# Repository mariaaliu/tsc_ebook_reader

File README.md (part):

## Aliu Maria-Denisa
#### 335CC
<br><br>

## Descriere generală
Acest proiect reprezintă un eBook Reader minimalist, denumit **OpenBook**, construit pe baza platformei **ESP32-C6** și echipat cu un ecran e-paper de **7.5 inch**, o baterie Li-Po, încărcare prin USB-C și butoane fizice pentru control.

Dispozitivul este proiectat să fie eficient energetic și ușor de utilizat, având o interfață simplă controlată prin GPIO-uri, cu funcții de afișare a textelor pentru o experiență de e-reading optimă.

---

<br><br>

## Cuprins
- [Specificații](#specificații)
- [Pași de implementare](#pași-de-implementare)
- [Diagramă Bloc](#diagramă-bloc)
- [BOM (Bill Of Materials)](#bom-bill-of-materials)
- [Descrierea hardware – Conexiuni și Funcționalitate](#descrierea-hardware--conexiuni-și-funcționalitate)
- [Pinout ESP32-C6](#pinout-esp32-c6)
- [Estimare Consum](#estimare-consum)
- [Vederi ale Prototipului](#vederi-ale-prototipului)

---

#### Specificații

- **MCU**: ESP32-C6 (Wi-Fi 6, BLE, RISC-V)
- **Ecran**: 7.8" E-paper
- **Stocare**: Slot microSD
- **Conectivitate**: Qwiic, USB-C
- **Senzori**: BME680 (temperatură, umiditate, gaz, presiune)
- **Alimentare**: Baterie Li-Po 3.7V, încărcare prin USB-C
- **RTC**: extern pentru consum redus în deep sleep
- **Control**: 3 butoane + LED

---
#### Pași de implementare:

- realizarea schemei electrice
- poziționarea pieselor pe PCB 2D
- realizarea modelului 3D
- simularea încadrării pieselor în carcasa finală
- prezentarea produsului final simulat
  
---

## Diagramă Bloc

```mermaid
graph TD;
    
    USB["USB-C Connector & ESD Protection"] -->|VBUS| CHG
    BATT["Li-Po Battery"] -->|VBAT| CHG["Battery Charging Controller (MCP73831)"]
    USB -->|VBUS pass-through| LDO["LDO Voltage Regulator (XC6220)"]
    USB -->|USB| ESP["ESP32-C6 MICROCONTROLLER Wi-Fi (MCU Central)"]
    CHG -->|VBAT| LDO
    LDO -->|3.3V| ESP["ESP32-C6 MICROCONTROLLER Wi-Fi (MCU Central)"]

    ESP -->|I2C| RTC["RTC Module (DS3231SN)"]
    ESP -->|I2C| BME["Environmental Sensor (BME680)"]

    ESP -->|SPI| FLASH["External NOR Flash (W25Q512)"]
    ESP -->|SPI| EPD_HEADER["E-Paper Display Header"]
    ESP -->|SPI| SD["MicroSD Card"]
    ESP -->|GPIO| BUTTONS["BOOT, CHANGE, RESET Buttons"]
    ESP -->|GPIO| VSUP["Voltage Supervisor + Reset/Boot IO"]

    EPD_HEADER -->|Power, SPI| EPD_DRIVER["E-Paper Drive Circuit"]
    EPD_DRIVER -->|Type Config| DISP_SEL["Display Type Selector"]
    EPD_DRIVER -->|High Voltage| EPD_POW["EPD Power Circuit"]

    I2C_CONN["Qwiic / Stemma QT"] -->|I2C| ESP
    BAT_LVL["Battery Charge Level"] -->|I2C| ESP
    SERCOM["RX/TX Serial Communication"] --> ESP
```

## BOM (Bill Of Materials)

| Componentă      | Proptietăți                 | Package                                | Link Purchase              | Datasheet                | 
|----------------|-------------------------|----------------------------------------|-----------------------------------|-----------------------------|
| BOOT_BUTTON    | BUTTON_CUSYOMV1         | MYBUTTON | https://industry.panasonic.com/global/en/products/control/switch/light-touch/number/evqpuj02k | https://www.es.co.th/Schemetic/PDF/EVQPUX02K.PDF|
| C1            | 100nF                  | ESP32_WROVER_EAGLE-LTSPICE_C0402       | https://componentsearchengine.com/part-view/CC0402MRX5R5BB106/YAGEO | https://www.farnell.com/datasheets/2167237.pdf|
| C10            | 100nF                  | ESP32_WROVER_EAGLE-LTSPICE_C0402       | https://componentsearchengine.com/part-view/CC0402MRX5R5BB106/YAGEO | https://www.farnell.com/datasheets/2167237.pdf|
| C10_SUPERCAP   | CPH3225A               | CAPCP3225X100N  | https://www.snapeda.com/parts/CPH3225A/Seiko+Instruments/view-part/?ref=eda | https://www.eaton.com/content/dam/eaton/products/electronic-components/resources/data-sheet/eaton-xt-supercapacitors-cylindrical-cells-data-sheet.pdf|
| C1_BAT         | 4.7uF                  | ESP32_WROVER_EAGLE-LTSPICE_C0402       | https://componentsearchengine.com/part-view/CC0402MRX5R5BB106/YAGEO | https://www.datasheets.com/part-details/ctc4-c-4-7uf-20--25v-exxelia-group-407015684#datasheet?srsltid=AfmBOopSxVESrdZ-JeJFYRuFdBfwBIXZfFTXDnvi5T4sC5myfTVXPCBc|
| C1_BAT1        | 4.7uF                  | ESP32_WROVER_EAGLE-LTSPICE_C0402       | https://componentsearchengine.com/part-view/CC0402MRX5R5BB106/YAGEO | https://www.datasheets.com/part-details/ctc4-c-4-7uf-20--25v-exxelia-group-407015684#datasheet?srsltid=AfmBOopSxVESrdZ-JeJFYRuFdBfwBIXZfFTXDnvi5T4sC5myfTVXPCBc|
| C1_BAT2        | 4.7uF                  | ESP32_WROVER_EAGLE-LTSPICE_C0402       | https://componentsearchengine.com/part-view/CC0402MRX5R5BB106/YAGEO | https://www.datasheets.com/part-details/ctc4-c-4-7uf-20--25v-exxelia-group-407015684#datasheet?srsltid=AfmBOopSxVESrdZ-JeJFYRuFdBfwBIXZfFTXDnvi5T4sC5myfTVXPCBc|
| C2             | 100nF                  | ESP32_WROVER_EAGLE-LTSPICE_C0402       | https://componentsearchengine.com/part-view/CC0402MRX5R5BB106/YAGEO | https://www.farnell.com/datasheets/2167237.pdf|
| C2_BAT        | 4.7uF                  | ESP32_WROVER_EAGLE-LTSPICE_C0402       | https://componentsearchengine.com/part-view/CC0402MRX5R5BB106/YAGEO | https://www.datasheets.com/part-details/ctc4-c-4-7uf-20--25v-exxelia-group-407015684#datasheet?srsltid=AfmBOopSxVESrdZ-JeJFYRuFdBfwBIXZfFTXDnvi5T4sC5myfTVXPCBc|
| C3            | 100uF                  | RCL_CT3528 | https://eu.mouser.com/ProductDetail/KYOCERA-AVX/F910J107MBAAJ6?qs=PqoDHHvF649LraCA%2FjeGXg%3D%3D | https://www.farnell.com/datasheets/2167237.pdf|
| C4             | 4.7uF/25V              | ESP32_WROVER_EAGLE-LTSPICE_C0402       | https://componentsearchengine.com/part-view/CC0402MRX5R5BB106/YAGEO | https://www.datasheets.com/part-details/ctc4-c-4-7uf-20--25v-exxelia-group-407015684#datasheet?srsltid=AfmBOopSxVESrdZ-JeJFYRuFdBfwBIXZfFTXDnvi5T4sC5myfTVXPCBc|
| C4_USB         | 100nF                  | ESP32_WROVER_EAGLE-LTSPICE_C0402       | https://componentsearchengine.com/part-view/CC0402MRX5R5BB106/YAGEO | https://www.farnell.com/datasheets/2167237.pdf|
| C5             | 1uF                    | ESP32_WROVER_EAGLE-LTSPICE_C0402       | https://componentsearchengine.com/part-view/CC0402MRX5R5BB106/YAGEO | https://www.farnell.com/datasheets/2167237.pdf|
| C5_USB         | 4.7uF                  | ESP32_WROVER_EAGLE-LTSPICE_C0402       | https://componentsearchengine.com/part-view/CC0402MRX5R5BB106/YAGEO | https://www.datasheets.com/part-details/ctc4-c-4-7uf-20--25v-exxelia-group-407015684#datasheet?srsltid=AfmBOopSxVESrdZ-JeJFYRuFdBfwBIXZfFTXDnvi5T4sC5myfTVXPCBc|
| C6             | 100nF                  | ESP32_WROVER_EAGLE-LTSPICE_C0402       | https://componentsearchengine.com/part-view/CC0402MRX5R5BB106/YAGEO | https://www.farnell.com/datasheets/2167237.pdf|
| C7             | 10uF                   | ESP32_WROVER_EAGLE-LTSPICE_C0402       | https://componentsearchengine.com/part-view/CC0402MRX5R5BB106/YAGEO | https://www.farnell.com/datasheets/2167237.pdf|
| C8             | 100nF                  | ESP32_WROVER_EAGLE-LTSPICE_C0402       | https://componentsearchengine.com/part-view/CC0402MRX5R5BB106/YAGEO | https://www.farnell.com/datasheets/2167237.pdf|
| C9            | 100nF                  | ESP32_WROVER_EAGLE-LTSPICE_C0402       | https://componentsearchengine.com/part-view/CC0402MRX5R5BB106/YAGEO | https://www.farnell.com/datasheets/2167237.pdf|
| CHANGE_BUTTON  | BUTTON_CUSYOMV1         | MYBUTTON | https://industry.panasonic.com/global/en/products/control/switch/light-touch/number/evqpuj02k | https://www.es.co.th/Schemetic/PDF/EVQPUX02K.PDF|
| CHG_LED        |                        | ADAFRUIT_CHIP-LED0603                  | https://www.snapeda.com/parts/KP-1608SURCK/Kingbright/view-part/?ref=search&t=LED%200603 | https://www.farnell.com/datasheets/1760130.pdf|
| C_DELAY        | 100nF                  | ESP32_WROVER_EAGLE-LTSPICE_C0402       | https://componentsearchengine.com/part-view/CC0402MRX5R5BB106/YAGEO | https://www.farnell.com/datasheets/2167237.pdf|
| D1             | USBLC6-2SC6Y            | SOT95P280X145-6N                       | https://www.snapeda.com/parts/USBLC6-2SC6Y/STMicroelectronics/view-part/?ref=eda | https://www.alldatasheet.com/view.jsp?Searchword=Usblc6-2sc6%20datasheet&gad_source=1&gclid=Cj0KCQjwqcO_BhDaARIsACz62vNXZrpQv2LPEwLifCXR-Z6ow5Jz23VCwAl6sagpvX4qBsG8mq23hT8aAgWJEALw_wcB|
| D10            | PGB1010603MR            | DIOC1608X36N                           | https://www.snapeda.com/parts/PGB1010603MR/Littelfuse/view-part/?ref=eda | https://www.alldatasheet.com/view.jsp?Searchword=Pgb1010603mr&gad_source=1&gclid=Cj0KCQjwqcO_BhDaARIsACz62vM1VI-TQZSchByLeU1DA3nQWoILlr1ci-3FtcNGSAGQc69Pgj3MI4oaAjWKEALw_wcB|
| D11            | PGB1010603MR            | DIOC1608X36N                           | https://www.snapeda.com/parts/PGB1010603MR/Littelfuse/view-part/?ref=eda | https://www.alldatasheet.com/view.jsp?Searchword=Pgb1010603mr&gad_source=1&gclid=Cj0KCQjwqcO_BhDaARIsACz62vM1VI-TQZSchByLeU1DA3nQWoILlr1ci-3FtcNGSAGQc69Pgj3MI4oaAjWKEALw_wcB|
| D12            | PGB1010603MR            | DIOC1608X36N                           | https://www.snapeda.com/parts/PGB1010603MR/Littelfuse/view-part/?ref=eda | https://www.alldatasheet.com/view.jsp?Searchword=Pgb1010603mr&gad_source=1&gclid=Cj0KCQjwqcO_BhDaARIsACz62vM1VI-TQZSchByLeU1DA3nQWoILlr1ci-3FtcNGSAGQc69Pgj3MI4oaAjWKEALw_wcB|
| D2             | ESP32_WROVER_AVX---SD0805S020S1R0_AVX_SD0805S020S1R0_0 | ESP32_WROVER_AVX---SD0805S020S1R0_AVX_SD0805S020S1R0_0 | https://ro.mouser.com/ProductDetail/KYOCERA-AVX/SD0805S020S1R0?qs=jCA%252BPfw4LHbpkAoSnwrdjw%3D%3D&utm_id=6470900573&utm_source=google&utm_medium=cpc&utm_marketing_tactic=emeacorp&gad_source=1&gclid=Cj0KCQjwqcO_BhDaARIsACz62vPEfi9ntBpuuK1LHM6sMAyEc2S6XwGXFRcoYK5gKMYya27spaEhkKEaAkeQEALw_wcB | https://www.alldatasheet.com/datasheet-pdf/pdf/925781/AVX/SD0805S020S1R0.html|
| D3             | MBR0530                 | SOD3716X135N                           | https://www.snapeda.com/parts/MBR0530/Onsemi/view-part/?ref=eda | https://www.alldatasheet.com/view.jsp?Searchword=Mbr0530%20datasheet&gad_source=1&gclid=Cj0KCQjwqcO_BhDaARIsACz62vP1swtUgHHaBr1h1Ae3TYdeqhmQC4x2pEdoGRj9oflsija9HAEBlBMaAvdlEALw_wcB|
| D4             | MBR0530                 | SOD3716X135N                           | https://www.snapeda.com/parts/MBR0530/Onsemi/view-part/?ref=eda | https://www.alldatasheet.com/view.jsp?Searchword=Mbr0530%20datasheet&gad_source=1&gclid=Cj0KCQjwqcO_BhDaARIsACz62vP1swtUgHHaBr1h1Ae3TYdeqhmQC4x2pEdoGRj9oflsija9HAEBlBMaAvdlEALw_wcB|
| D5             | MBR0530                 | SOD3716X135N                           | https://www.snapeda.com/parts/MBR0530/Onsemi/view-part/?ref=eda | https://www.alldatasheet.com/view.jsp?Searchword=Mbr0530%20datasheet&gad_source=1&gclid=Cj0KCQjwqcO_BhDaARIsACz62vP1swtUgHHaBr1h1Ae3TYdeqhmQC4x2pEdoGRj9oflsija9HAEBlBMaAvdlEALw_wcB|
| D6             | PGB1010603MR            | DIOC1608X36N                           | https://www.snapeda.com/parts/PGB1010603MR/Littelfuse/view-part/?ref=eda | https://www.alldatasheet.com/view.jsp?Searchword=Pgb1010603mr&gad_source=1&gclid=Cj0KCQjwqcO_BhDaARIsACz62vM1VI-TQZSchByLeU1DA3nQWoILlr1ci-3FtcNGSAGQc69Pgj3MI4oaAjWKEALw_wcB|
| D7             | ESP32_WROVER_AVX---SD0805S020S1R0_AVX_SD0805S020S1R0_0 | ESP32_WROVER_AVX---SD0805S020S1R0_AVX_SD0805S020S1R0_0 | https://eu.mouser.com/ProductDetail/KYOCERA-AVX/SD0805S020S1R0?qs=jCA%252BPfw4LHbpkAoSnwrdjw%3D%3D | https://www.alldatasheet.com/datasheet-pdf/pdf/925781/AVX/SD0805S020S1R0.html|
| D8             | PGB1010603MR            | DIOC1608X36N                           | https://www.snapeda.com/parts/PGB1010603MR/Littelfuse/view-part/?ref=eda | https://www.alldatasheet.com/view.jsp?Searchword=Pgb1010603mr&gad_source=1&gclid=Cj0KCQjwqcO_BhDaARIsACz62vM1VI-TQZSchByLeU1DA3nQWoILlr1ci-3FtcNGSAGQc69Pgj3MI4oaAjWKEALw_wcB|
| D9             | PGB1010603MR            | DIOC1608X36N                           | https://www.snapeda.com/parts/PGB1010603MR/Littelfuse/view-part/?ref=eda |   https://www.alldatasheet.com/view.jsp?Searchword=Pgb1010603mr&gad_source=1&gclid=Cj0KCQjwqcO_BhDaARIsACz62vM1VI-TQZSchByLeU1DA3nQWoILlr1ci-3FtcNGSAGQc69Pgj3MI4oaAjWKEALw_wcB|
| EPD_C1         | 1uF/50V                | ESP32_WROVER_EAGLE-LTSPICE_C0402       | https://componentsearchengine.com/part-view/CC0402MRX5R5BB106/YAGEO | https://www.alldatasheet.com/view.jsp?Searchword=Cc0402&gad_source=1&gclid=Cj0KCQjwqcO_BhDaARIsACz62vOHh9yg0g_xZhcu9_CEKANvUYtGv2kGtbzHYiw6TGDxPK-tL5UACRUaArTeEALw_wcB|
| EPD_C10        | 1uF/50V                | ESP32_WROVER_EAGLE-LTSPICE_C0402       | https://componentsearchengine.com/part-view/CC0402MRX5R5BB106/YAGEO | https://www.alldatasheet.com/view.jsp?Searchword=Cc0402&gad_source=1&gclid=Cj0KCQjwqcO_BhDaARIsACz62vOHh9yg0g_xZhcu9_CEKANvUYtGv2kGtbzHYiw6TGDxPK-tL5UACRUaArTeEALw_wcB|
| EPD_C11        | 1uF/50V                | ESP32_WROVER_EAGLE-LTSPICE_C0402       | https://componentsearchengine.com/part-view/CC0402MRX5R5BB106/YAGEO | https://www.farnell.com/datasheets/2167237.pdf|
| EPD_C12        | 1uF/50V                | ESP32_WROVER_EAGLE-LTSPICE_C0402       |   https://componentsearchengine.com/part-view/CC0402MRX5R5BB106/YAGEO | https://www.farnell.com/datasheets/2167237.pdf|
| EPD_C2         | 1uF/50V                | ESP32_WROVER_EAGLE-LTSPICE_C0402       |   https://componentsearchengine.com/part-view/CC0402MRX5R5BB106/YAGEO | https://www.farnell.com/datasheets/2167237.pdf|
| EPD_C5         | 1uF/50V                | ESP32_WROVER_EAGLE-LTSPICE_C0402       |   https://componentsearchengine.com/part-view/CC0402MRX5R5BB106/YAGEO | https://www.farnell.com/datasheets/2167237.pdf|
| EPD_C6         | 1uF/50V                | ESP32_WROVER_EAGLE-LTSPICE_C0402       |   https://componentsearchengine.com/part-view/CC0402MRX5R5BB106/YAGEO | https://www.farnell.com/datasheets/2167237.pdf|
| EPD_C7         | 1uF/50V                | ESP32_WROVER_EAGLE-LTSPICE_C0402       |   https://componentsearchengine.com/part-view/CC0402MRX5R5BB106/YAGEO | https://www.farnell.com/datasheets/2167237.pdf|
| EPD_C8         | 1uF/50V                | ESP32_WROVER_EAGLE-LTSPICE_C0402       |   https://componentsearchengine.com/part-view/CC0402MRX5R5BB106/YAGEO | https://www.farnell.com/datasheets/2167237.pdf|
| EPD_C9         | 1uF/50V                | ESP32_WROVER_EAGLE-LTSPICE_C0402       |   https://componentsearchengine.com/part-view/CC0402MRX5R5BB106/YAGEO | https://www.farnell.com/datasheets/2167237.pdf|
| IC1            | BD5229G-TR             | SOT95P280X125-5N                       | https://componentsearchengine.com/part-view/BD5229G-TR/ROHM%20Semiconductor | https://www.alldatasheet.com/datasheet-pdf/pdf/562784/ROHM/BD5229G-TR.html|
| IC4            | XC6220A331MR-G         | SOT95P280X120-5N | https://componentsearchengine.com/part-view/XC6220A331MR-G/Torex | https://www.alldatasheet.com/view.jsp?Searchword=Xc6220&gad_source=1&gclid=Cj0KCQjwqcO_BhDaARIsACz62vNFXNXymZGlzcmkfMZCs0YXLAkJ5yWCPMtu7VvrTb50o02U6EU8bI8aAu8CEALw_wcB|
| J1        | FH34SRJ-24S-0.5SH_99_ | FH34SRJ24S05SH99                               | https://componentsearchengine.com/part-view/FH34SRJ-24S-0.5SH(99)/Hirose | https://ro.mouser.com/ProductDetail/Hirose-Connector/FH34S-24S-05SH99?qs=sGAEpiMZZMtarqWRZQNdzRgjNobWj1V%252b&srsltid=AfmBOopOc7xnQo8WmFAadUKxs2Pv_ZRqS0lJLFK245RRjT5g5CQNT84v|
| J2        | SAMACSYS_PARTS_USB4110-GF-A | SAMACSYS_PARTS_USB4110GFA                     | https://componentsearchengine.com/part-view/USB4110-GF-A/GCT%20(GLOBAL%20CONNECTOR%20TECHNOLOGY) | https://www.lcsc.com/datasheet/lcsc_datasheet_2410121848_Global-Connector-Technology-USB4110-GF-A_C5143397.pdf|
| J3        | QWIIC_RIGHT_ANGLE | JST04_1MM_RA                                  | https://eu.mouser.com/ProductDetail/Adafruit/4208?qs=PzGy0jfpSMtbScLbr0L5dw%3D%3D | ...|
| J4        | 112A-TAAR-R03_ATTEND | 112ATAARR03ATTEND                             | https://store.comet.srl.ro/Catalogue/Product/43497/ | https://www.lcsc.com/datasheet/lcsc_datasheet_2411220717_Attend-Technology-112A-TAAR-R03_C6970445.pdf|
| L1        | 68uH            | IND_4828-WE-TPC_WRE                           | https://eu.mouser.com/ProductDetail/Wurth-Elektronik/744043680?qs=PGXP4M47uW6VkZq%252BkzjrHA%3D%3D | https://in.element14.com/c/passive-components/inductors/power-inductors/smd-power-inductors?inductance=68uh&srsltid=AfmBOoqYXGbL9sGdZ46Hro8CihzXM-LXkKuWlFwNsDA_NlrY7XGM2FaG|
| MCP73831  | ESP32_WROVER_SPARKFUN-IC-POWER_MCP73831 | ESP32_WROVER_SPARKFUN-IC-POWER_SOT23-5 | https://eu.mouser.com/ProductDetail/Microchip-Technology/MCP73831T-2ACI-OT?qs=yUQqVecv4qvbBQBGbHx0Mw%3D%3D | https://www.alldatasheet.com/view.jsp?Searchword=Mcp73831%20datasheet&gad_source=1&gclid=Cj0KCQjwqcO_BhDaARIsACz62vNE_GnTDdT47-u9Q2OgRK9TX-D7V258Eoba7KxX2pQKwTPrbfjDHwUaAgovEALw_wcB|
| PFMF.050.1| ESP32C6_VARISTORCN1812 | ESP32C6_VARISTOR_CT/CN1812                    | https://www.mouser.co.uk/ProductDetail/EPCOS-TDK/B72520T0350K062?qs=dEfas%2FXlABIszF52uu7vrg%3D%3D | https://www.alldatasheet.com/datasheet-pdf/pdf/356683/SCHURTER/PFMF.050.2.html|
| Q1        | 20V/4.2A/52mΩ/1.4W | ESP32_WROVER_SPARKFUN-DISCRETESEMI_SOT23-3    | https://componentsearchengine.com/part-view/DMG2305UX-7/Diodes%20Incorporated | https://www.alldatasheet.com/view.jsp?Searchword=Dmg2305ux%20datasheet&gad_source=1&gclid=Cj0KCQjwqcO_BhDaARIsACz62vMQW1FwcgD0y0qdHMHKzUlJHlz1eBpHMgg3QfZKxp4WrlQYG_-XCGgaApFcEALw_wcB|
| Q2        | 20V/4.2A/52mΩ/1.4W | ESP32_WROVER_SPARKFUN-DISCRETESEMI_SOT23-3    | https://componentsearchengine.com/part-view/DMG2305UX-7/Diodes%20Incorporated | https://www.alldatasheet.com/view.jsp?Searchword=Dmg2305ux%20datasheet&gad_source=1&gclid=Cj0KCQjwqcO_BhDaARIsACz62vMQW1FwcgD0y0qdHMHKzUlJHlz1eBpHMgg3QfZKxp4WrlQYG_-XCGgaApFcEALw_wcB|
| Q3        | SI1308EDL-T1-GE3 | SOT65P210X110-3N                              | https://www.snapeda.com/parts/SI1308EDL-T1-GE3/Vishay+Siliconix/view-part/?ref=eda | https://www.alldatasheet.com/view.jsp?Searchword=Si1308edl&gad_source=1&gclid=Cj0KCQjwqcO_BhDaARIsACz62vM_bGjumR2fFnx6qeTFOw_xlZ569sW-bMnlphTnUfPy48QznN7oXRgaAuROEALw_wcB|
| R1        | 10K             | ESP32_WROVER_EAGLE-LTSPICE_R0402              | https://componentsearchengine.com/part-view/R0402%201%25%20100%20K%20(RC0402FR-07100KL)/YAGEO | https://ro.farnell.com/c/passive-components/resistors-fixed-value/chip-smd-resistors?resistance=10kohm&srsltid=AfmBOoppk2KzsJ9X9eQ3Cprqx-aidJD_GTPJgWaEEgH3df9fBymJm3mo|
| R10       | 10K             | ESP32_WROVER_EAGLE-LTSPICE_R0402              | https://componentsearchengine.com/part-view/R0402%201%25%20100%20K%20(RC0402FR-07100KL)/YAGEO | https://ro.farnell.com/c/passive-components/resistors-fixed-value/chip-smd-resistors?resistance=10kohm&srsltid=AfmBOoppk2KzsJ9X9eQ3Cprqx-aidJD_GTPJgWaEEgH3df9fBymJm3mo|
| R1_BAT    | 200             | ESP32_WROVER_EAGLE-LTSPICE_R0402              | https://ro.mouser.com/c/passive-components/resistors/smd-resistors-chip-resistors/?case%20code%20-%20in=0402&resistance=200%20Ohms&srsltid=AfmBOoo-6O-URQcmQGAwWvWkSloJBGjVxIwzoZir5TS3KZAaaRmw5_VT | https://www.farnell.com/datasheets/2167237.pdf|
| R1_PINH   | 10K             | ESP32_WROVER_EAGLE-LTSPICE_R0402              | https://componentsearchengine.com/part-view/R0402%201%25%20100%20K%20(RC0402FR-07100KL)/YAGEO | https://ro.farnell.com/c/passive-components/resistors-fixed-value/chip-smd-resistors?resistance=10kohm&srsltid=AfmBOoppk2KzsJ9X9eQ3Cprqx-aidJD_GTPJgWaEEgH3df9fBymJm3mo|
| R1_PINH1  | 10K             | ESP32_WROVER_EAGLE-LTSPICE_R0402              | https://componentsearchengine.com/part-view/R0402%201%25%20100%20K%20(RC0402FR-07100KL)/YAGEO | https://ro.farnell.com/c/passive-components/resistors-fixed-value/chip-smd-resistors?resistance=10kohm&srsltid=AfmBOoppk2KzsJ9X9eQ3Cprqx-aidJD_GTPJgWaEEgH3df9fBymJm3mo|
| R1_PWRUSB | 100k            | ESP32_WROVER_EAGLE-LTSPICE_R0402              | https://componentsearchengine.com/part-view/R0402%201%25%20100%20K%20(RC0402FR-07100KL)/YAGEO | https://ro.farnell.com/c/passive-components/resistors-fixed-value/chip-smd-resistors?resistance=10kohm&srsltid=AfmBOoppk2KzsJ9X9eQ3Cprqx-aidJD_GTPJgWaEEgH3df9fBymJm3mo|
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
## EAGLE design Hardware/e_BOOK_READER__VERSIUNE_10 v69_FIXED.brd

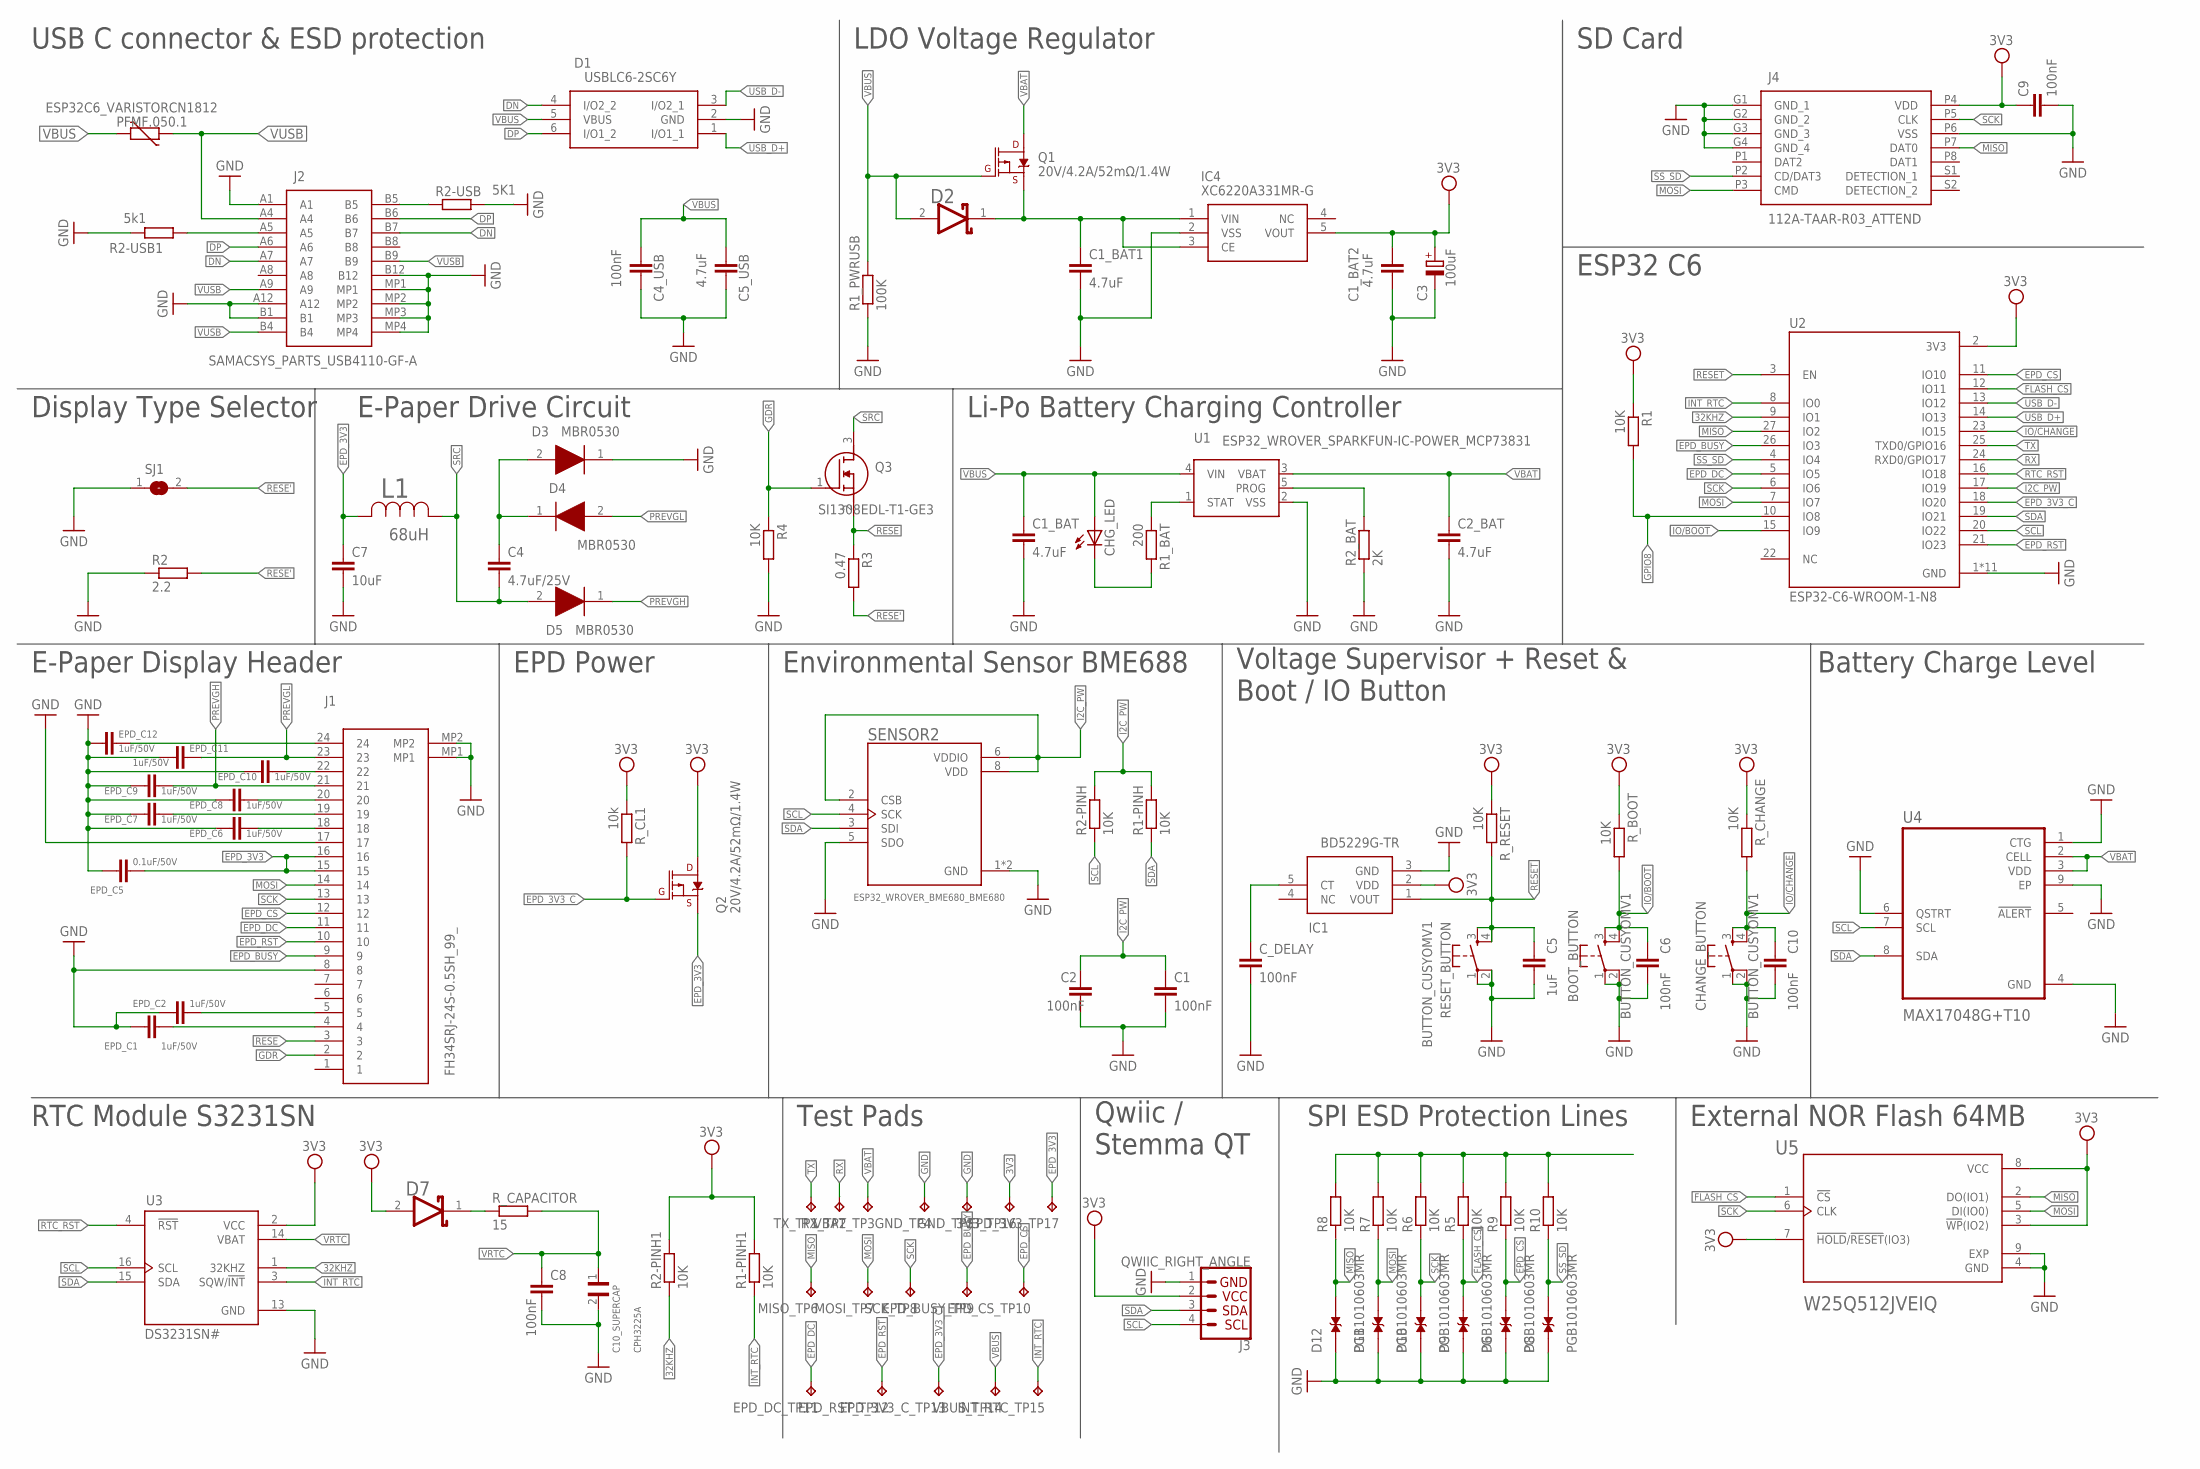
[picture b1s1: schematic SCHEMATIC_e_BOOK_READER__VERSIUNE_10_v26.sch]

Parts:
3V3_TP16: TPTP20R; TP20R
BOOT_BUTTON: BUTTON_CUSYOMV1; MYBUTTON
C1, C2, C4_USB, C6, C8, C9, C10: 100nF; ESP32_WROVER_EAGLE-LTSPICE_C0402
C1_BAT, C1_BAT1, C1_BAT2, C2_BAT, C5_USB: 4.7uF; ESP32_WROVER_EAGLE-LTSPICE_C0402
C3: 100uF; RCL_CT3528
C4: 4.7uF/25V; ESP32_WROVER_EAGLE-LTSPICE_C0402
C5: 1uF; ESP32_WROVER_EAGLE-LTSPICE_C0402
C7: 10uF; ESP32_WROVER_EAGLE-LTSPICE_C0402
C10_SUPERCAP: CPH3225A; CAPCP3225X100N
CHANGE_BUTTON: BUTTON_CUSYOMV1; MYBUTTON
CHG_LED: ADAFRUIT_LEDCHIP-LED0603; ADAFRUIT_CHIP-LED0603
C_DELAY: 100nF; ESP32_WROVER_EAGLE-LTSPICE_C0402
D1: USBLC6-2SC6Y; SOT95P280X145-6N
D2, D7: ESP32_WROVER_AVX---SD0805S020S1R0_AVX_SD0805S020S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; ESP32_WROVER_AVX---SD0805S020S1R0_AVX_SD0805S020S1R0_0
D3, D4, D5: MBR0530; ESP32_WROVER_AVX---SD0805S020S1R0_AVX_SD0805S020S1R0_0
D6, D8, D9, D10, D11, D12: PGB1010603MR; DIOC1608X36N
EPD_3V3_C_TP13, EPD_3V3_TP17: TPTP20R; TP20R
EPD_BUSY_TP9: TPTP20R; TP20R
EPD_C1, EPD_C2, EPD_C6, EPD_C7, EPD_C8, EPD_C9, EPD_C10, EPD_C11, EPD_C12: 1uF/50V; ESP32_WROVER_EAGLE-LTSPICE_C0402
EPD_C5: 0.1uF/50V; ESP32_WROVER_EAGLE-LTSPICE_C0402
EPD_CS_TP10: TPTP20R; TP20R
EPD_DC_TP11: TPTP20R; TP20R
EPD_RST_TP12: TPTP20R; TP20R
GND_TP4, GND_TP5: TPTP20R; TP20R
IC1: BD5229G-TR; SOT95P280X125-5N
IC4: XC6220A331MR-G; SOT95P280X120-5N
INT_RTC_TP15: TPTP20R; TP20R
J1: FH34SRJ-24S-0.5SH_99_; FH34SRJ24S05SH99
J2: SAMACSYS_PARTS_USB4110-GF-A; SAMACSYS_PARTS_USB4110GFA
J3: QWIIC_RIGHT_ANGLE; JST04_1MM_RA
J4: 112A-TAAR-R03_ATTEND; 112ATAARR03ATTEND
L1: 68uH; IND_4828-WE-TPC_WRE
MISO_TP6: TPTP20R; TP20R
MOSI_TP7: TPTP20R; TP20R
PFMF.050.1: ESP32C6_VARISTORCN1812; ESP32C6_VARISTOR_CT/CN1812
Q1, Q2: 20V/4.2A/52mΩ/1.4W; ESP32_WROVER_SPARKFUN-DISCRETESEMI_SOT23-3
Q3: SI1308EDL-T1-GE3; SOT65P210X110-3N
R1, R1-PINH, R1-PINH1, R2-PINH, R2-PINH1, R4, R5, R6, R7, R8, R9, R10: 10K; ESP32_WROVER_EAGLE-LTSPICE_R0402
R1_BAT: 200; ESP32_WROVER_EAGLE-LTSPICE_R0402
R1_PWRUSB: 100K; ESP32_WROVER_EAGLE-LTSPICE_R0402
R2: 2.2; ESP32_WROVER_EAGLE-LTSPICE_R0402
R2-USB: 5K1; ESP32_WROVER_EAGLE-LTSPICE_R0402
R2-USB1: 5k1; ESP32_WROVER_EAGLE-LTSPICE_R0402
R2_BAT: 2K; ESP32_WROVER_EAGLE-LTSPICE_R0402
R3: 0.47; ESP32_WROVER_EAGLE-LTSPICE_R0402
RESET_BUTTON: BUTTON_CUSYOMV1; MYBUTTON
RX_TP2: TPTP20R; TP20R
R_BOOT: 10K; ESP32_WROVER_EAGLE-LTSPICE_R0402
R_CAPACITOR: 15; ESP32_WROVER_EAGLE-LTSPICE_R0402
R_CHANGE: 10K; ESP32_WROVER_EAGLE-LTSPICE_R0402
R_CL1: 10k; ESP32_WROVER_EAGLE-LTSPICE_R0402
R_RESET: 10K; ESP32_WROVER_EAGLE-LTSPICE_R0402
SCK_TP8: TPTP20R; TP20R
SENSOR2: ESP32_WROVER_BME680_BME680; ESP32_WROVER_BME680_PSON80P300X300X100-8N
SJ1: SJ
TX_TP1: TPTP20R; TP20R
U1: ESP32_WROVER_SPARKFUN-IC-POWER_MCP73831; ESP32_WROVER_SPARKFUN-IC-POWER_SOT23-5
U2: ESP32-C6-WROOM-1-N8; XCVR_ESP32-C6-WROOM-1-N8
U3: DS3231SN#; SOIC127P1032X265-16N
U4: MAX17048G+T10; SON50P200X200X80-9N
U5: W25Q512JVEIQ; SON127P600X800X80-9N
VBAT_TP3: TPTP20R; TP20R
VBUS_TP14: TPTP20R; TP20R

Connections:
3V3: 3V3_TP16.TP, C1_BAT2.1, C3.+, C9.1, D7.2 (ANODE), IC1.2 (VDD), IC4.5 (VOUT), J3.2, J4.P4 (VDD), Q2.3 (D), R1.1, R1-PINH1.2, R2-PINH1.2, R_BOOT.1, R_CHANGE.1, R_CL1.1, R_RESET.1, U2.2 (3V3), U3.2 (VCC), U5.3 (!WP!(IO2)), U5.7 (!HOLD!/!RESET!(IO3)), U5.8 (VCC)
32KHZ: R2-PINH1.1, U2.9 (IO1), U3.1 (32KHZ)
DN: D1.4 (I/O2_2), J2.A7, J2.B7
DP: D1.6 (I/O1_2), J2.A6, J2.B6
EPD_3V3: C7.1, EPD_3V3_TP17.TP, EPD_C5.1, J1.15, J1.16, L1.2, Q2.2 (S)
EPD_3V3_C: EPD_3V3_C_TP13.TP, Q2.1 (G), R_CL1.2, U2.18 (IO20)
EPD_BUSY: EPD_BUSY_TP9.TP, J1.9, U2.26 (IO3)
EPD_CS: D6.2, EPD_CS_TP10.TP, J1.12, R9.1, U2.11 (IO10)
EPD_DC: EPD_DC_TP11.TP, J1.11, U2.5 (IO5)
EPD_RST: EPD_RST_TP12.TP, J1.10, U2.21 (IO23)
FLASH_CS: D9.2, R5.1, U2.12 (IO11), U5.1 (!CS)
GDR: J1.2, Q3.1 (G), R4.1
GPIO8: R1.2, U2.10 (IO8)
I2C_PW: C1.1, C2.1, R1-PINH.2, R2-PINH.2, SENSOR2.2 (CSB), SENSOR2.6 (VDDIO), SENSOR2.8 (VDD), U2.17 (IO19)
INT_RTC: INT_RTC_TP15.TP, R1-PINH1.1, U2.8 (IO0), U3.3 (SQW/!INT)
IO/BOOT: BOOT_BUTTON.3, BOOT_BUTTON.4, C6.1, R_BOOT.2, U2.15 (IO9)
IO/CHANGE: C10.1, CHANGE_BUTTON.3, CHANGE_BUTTON.4, R_CHANGE.2, U2.23 (IO15)
MISO: D12.2, J4.P7 (DAT0), MISO_TP6.TP, R8.1, U2.27 (IO2), U5.2 (DO(IO1))
MOSI: D11.2, J1.14, J4.P3 (CMD), MOSI_TP7.TP, R7.1, U2.7 (IO7), U5.5 (DI(IO0))
unnamed: C1_BAT1.1, D2.1 (CATHODE), IC4.1 (VIN), IC4.3 (CE), Q1.2 (S)
unnamed: J2.A5, R2-USB1.2
unnamed: R5.2, R6.2, R7.2, R8.2, R9.2, R10.2
unnamed: R1_BAT.1, U1.1 (STAT)
unnamed: C4.1, D3.2 (A), D4.1 (K)
unnamed: CHG_LED.C, R1_BAT.2
unnamed: D7.1 (CATHODE), R_CAPACITOR.1
unnamed: J2.B5, R2-USB.1
unnamed: C_DELAY.1, IC1.5 (CT)
unnamed: EPD_C12.1, J1.24
unnamed: R2_BAT.2, U1.5 (PROG)
unnamed: EPD_C8.1, J1.20
unnamed: EPD_C10.1, J1.22
unnamed: EPD_C7.1, J1.19
unnamed: EPD_C6.1, J1.18
unnamed: EPD_C1.1, J1.4
unnamed: EPD_C2.1, J1.5
PREVGH: D5.1 (K), EPD_C9.1, J1.21
PREVGL: D4.2 (A), EPD_C11.1, J1.23
RESE: J1.3, Q3.2 (S), R3.1
RESE': R2.2, R3.2, SJ1.2
RESET: C5.1, IC1.1 (VOUT), RESET_BUTTON.3, RESET_BUTTON.4, R_RESET.2, U2.3 (EN)
RTC_RST: U2.16 (IO18), U3.4 (!RST)
RX: RX_TP2.TP, U2.24 (RXD0/GPIO17)
SCK: D10.2, J1.13, J4.P5 (CLK), R6.1, SCK_TP8.TP, U2.6 (IO6), U5.6 (CLK)
SCL: J3.4, R2-PINH.1, SENSOR2.4 (SCK), U2.20 (IO22), U3.16 (SCL), U4.7 (SCL)
SDA: J3.3, R1-PINH.1, SENSOR2.3 (SDI), U2.19 (IO21), U3.15 (SDA), U4.8 (SDA)
SRC: C4.2, D5.2 (A), L1.1, Q3.3 (D)
SS_SD: D8.2, J4.P2 (CD/DAT3), R10.1, U2.4 (IO4)
TX: TX_TP1.TP, U2.25 (TXD0/GPIO16)
USB_D+: D1.1 (I/O1_1), U2.14 (IO13)
USB_D-: D1.3 (I/O2_1), U2.13 (IO12)
VBAT: C2_BAT.1, Q1.3 (D), U1.3 (VBAT), U4.2 (CELL), U4.3 (VDD), VBAT_TP3.TP
VBUS: C1_BAT.1, C4_USB.1, C5_USB.1, CHG_LED.A, D1.5 (VBUS), D2.2 (ANODE), PFMF.050.1.2, Q1.1 (G), R1_PWRUSB.2, U1.4 (VIN), VBUS_TP14.TP
VUSB: J2.A4, J2.A9, J2.B4, J2.B9, PFMF.050.1.1

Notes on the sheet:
USB C connector & ESD protection
LDO Voltage Regulator
SD Card
ESP32 C6
Display Type Selector
E-Paper Drive Circuit
Li-Po Battery Charging Controller
E-Paper Display Header
EPD Power
Environmental Sensor BME688
Voltage Supervisor + Reset & Boot / IO Button
Battery Charge Level
RTC Module S3231SN
Test Pads
Qwiic / Stemma QT
SPI ESD Protection Lines
External NOR Flash 64MB

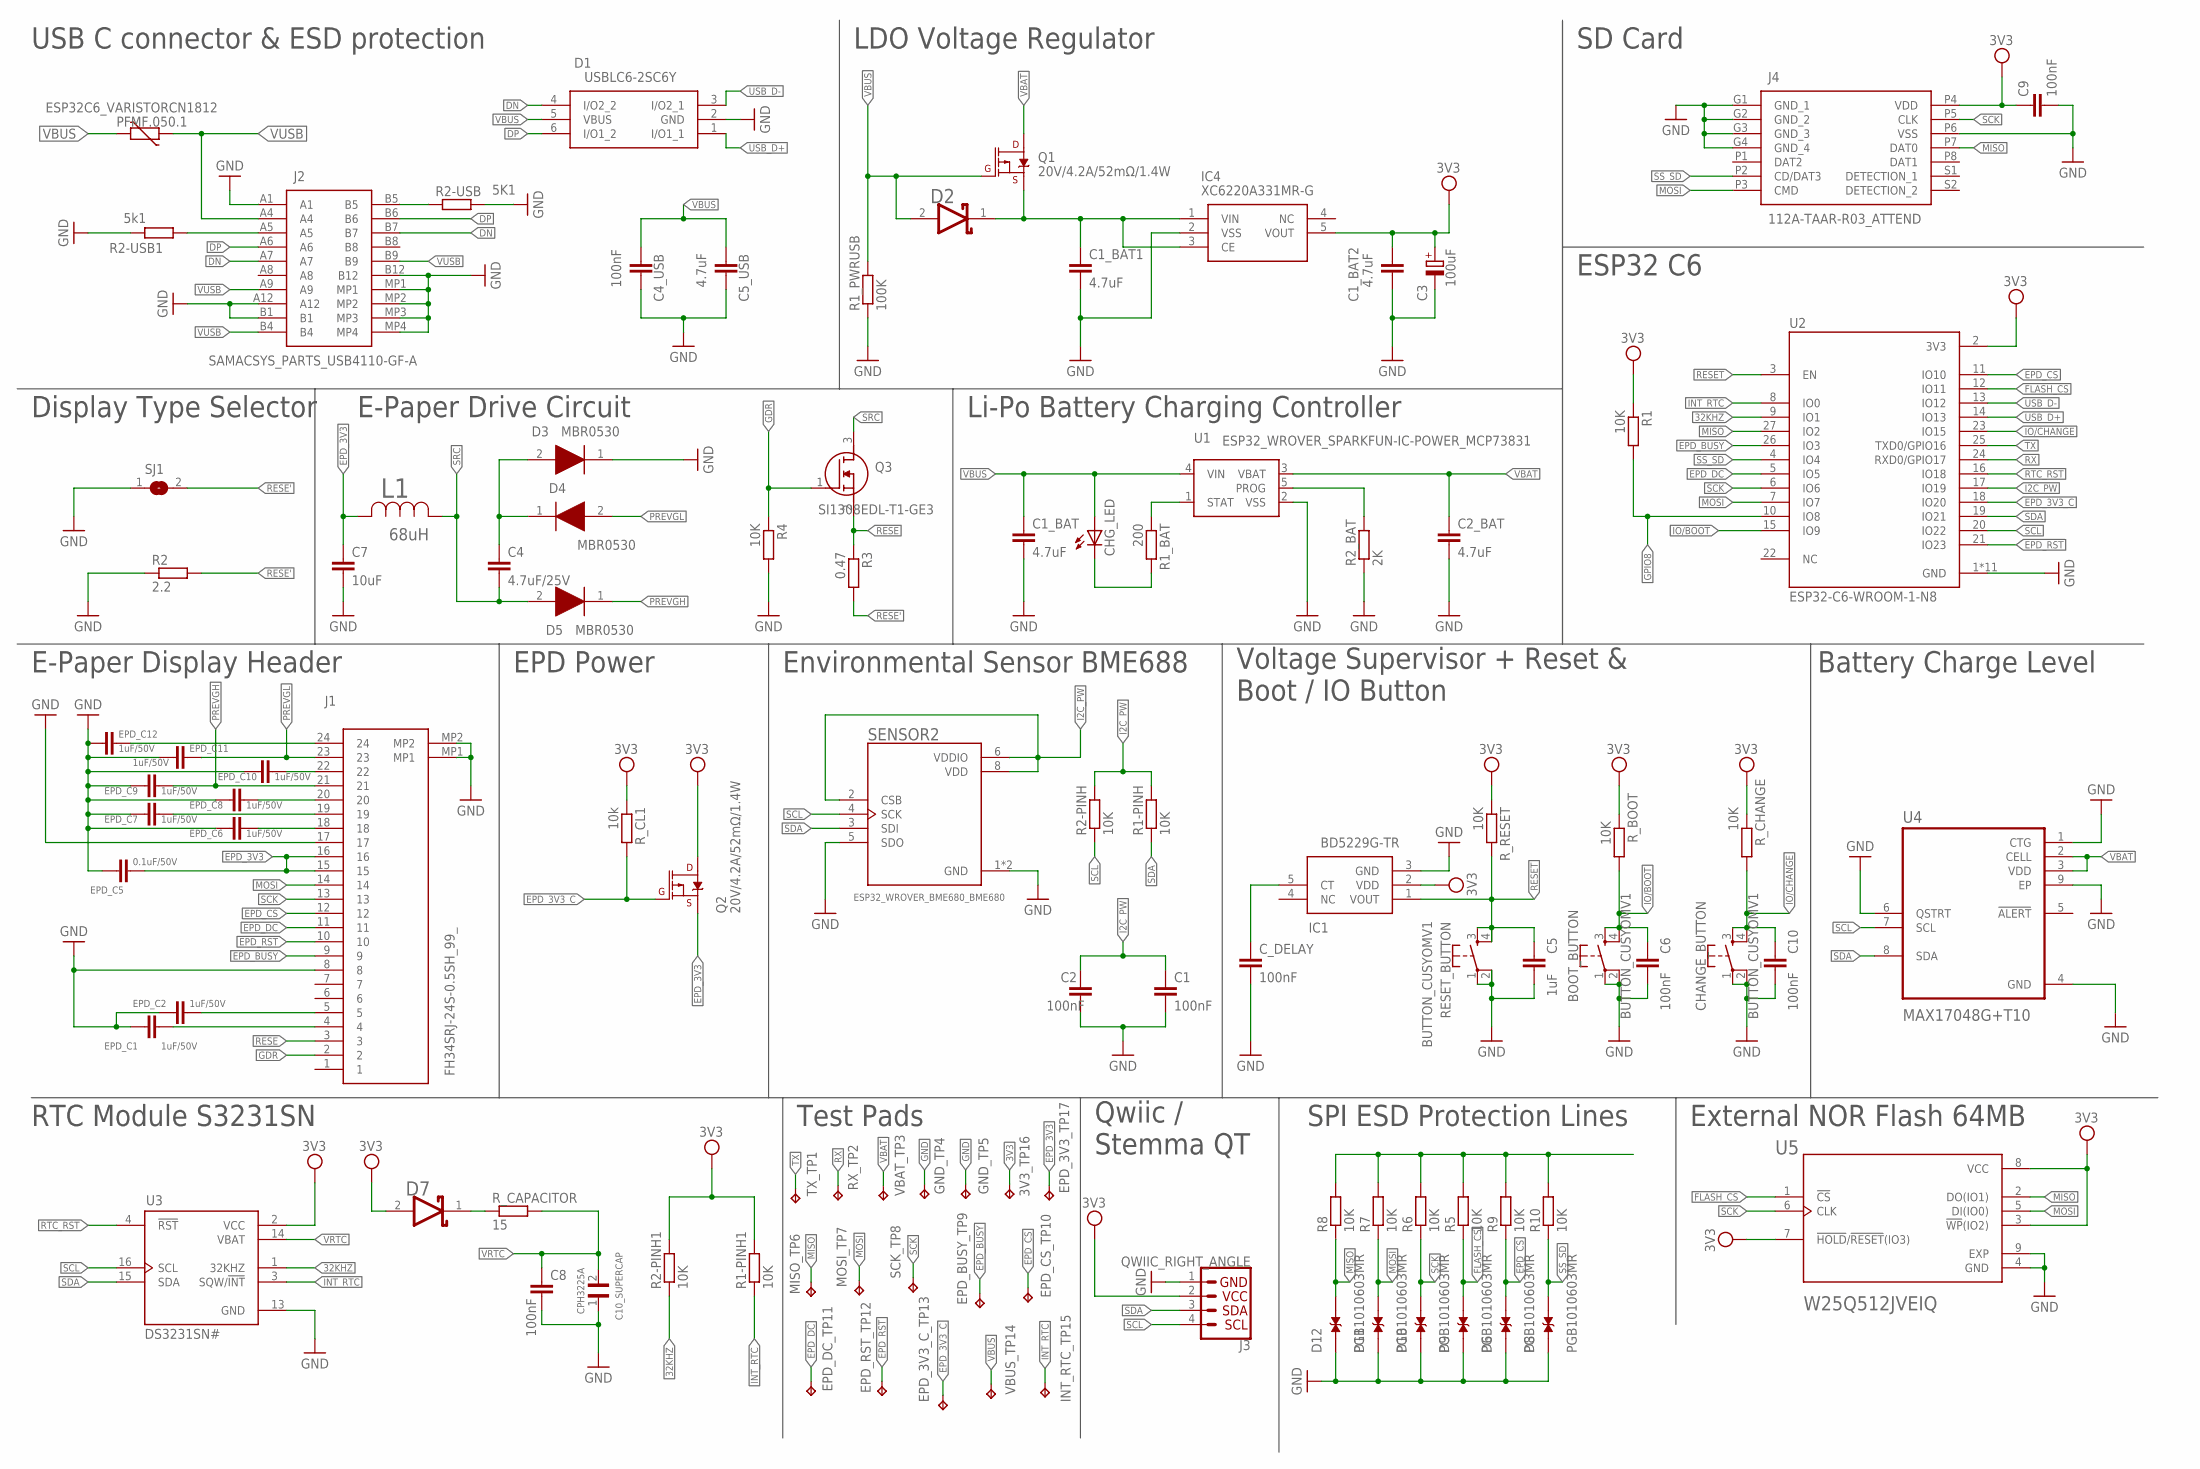
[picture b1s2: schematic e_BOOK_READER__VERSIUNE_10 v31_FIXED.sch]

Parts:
3V3_TP16: TPTP20R; TP20R
BOOT_BUTTON: BUTTON_CUSYOMV1; MYBUTTON
C1, C2, C4_USB, C6, C8, C9, C10: 100nF; ESP32_WROVER_EAGLE-LTSPICE_C0402
C1_BAT, C1_BAT1, C1_BAT2, C2_BAT, C5_USB: 4.7uF; ESP32_WROVER_EAGLE-LTSPICE_C0402
C3: 100uF; RCL_CT3528
C4: 4.7uF/25V; ESP32_WROVER_EAGLE-LTSPICE_C0402
C5: 1uF; ESP32_WROVER_EAGLE-LTSPICE_C0402
C7: 10uF; ESP32_WROVER_EAGLE-LTSPICE_C0402
C10_SUPERCAP: CPH3225A; CAPCP3225X100N
CHANGE_BUTTON: BUTTON_CUSYOMV1; MYBUTTON
CHG_LED: ADAFRUIT_LEDCHIP-LED0603; ADAFRUIT_CHIP-LED0603
C_DELAY: 100nF; ESP32_WROVER_EAGLE-LTSPICE_C0402
D1: USBLC6-2SC6Y; SOT95P280X145-6N
D2, D7: ESP32_WROVER_AVX---SD0805S020S1R0_AVX_SD0805S020S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; ESP32_WROVER_AVX---SD0805S020S1R0_AVX_SD0805S020S1R0_0
D3, D4, D5: MBR0530; ESP32_WROVER_AVX---SD0805S020S1R0_AVX_SD0805S020S1R0_0
D6, D8, D9, D10, D11, D12: PGB1010603MR; DIOC1608X36N
EPD_3V3_C_TP13, EPD_3V3_TP17: TPTP20R; TP20R
EPD_BUSY_TP9: TPTP20R; TP20R
EPD_C1, EPD_C2, EPD_C6, EPD_C7, EPD_C8, EPD_C9, EPD_C10, EPD_C11, EPD_C12: 1uF/50V; ESP32_WROVER_EAGLE-LTSPICE_C0402
EPD_C5: 0.1uF/50V; ESP32_WROVER_EAGLE-LTSPICE_C0402
EPD_CS_TP10: TPTP20R; TP20R
EPD_DC_TP11: TPTP20R; TP20R
EPD_RST_TP12: TPTP20R; TP20R
GND_TP4, GND_TP5: TPTP20R; TP20R
IC1: BD5229G-TR; SOT95P280X125-5N
IC4: XC6220A331MR-G; SOT95P280X120-5N
INT_RTC_TP15: TPTP20R; TP20R
J1: FH34SRJ-24S-0.5SH_99_; FH34SRJ24S05SH99
J2: SAMACSYS_PARTS_USB4110-GF-A; SAMACSYS_PARTS_USB4110GFA
J3: QWIIC_RIGHT_ANGLE; JST04_1MM_RA
J4: 112A-TAAR-R03_ATTEND; 112ATAARR03ATTEND
L1: 68uH; IND_4828-WE-TPC_WRE
MISO_TP6: TPTP20R; TP20R
MOSI_TP7: TPTP20R; TP20R
PFMF.050.1: ESP32C6_VARISTORCN1812; ESP32C6_VARISTOR_CT/CN1812
Q1, Q2: 20V/4.2A/52mΩ/1.4W; ESP32_WROVER_SPARKFUN-DISCRETESEMI_SOT23-3
Q3: SI1308EDL-T1-GE3; SOT65P210X110-3N
R1, R1-PINH, R1-PINH1, R2-PINH, R2-PINH1, R4, R5, R6, R7, R8, R9, R10: 10K; ESP32_WROVER_EAGLE-LTSPICE_R0402
R1_BAT: 200; ESP32_WROVER_EAGLE-LTSPICE_R0402
R1_PWRUSB: 100K; ESP32_WROVER_EAGLE-LTSPICE_R0402
R2: 2.2; ESP32_WROVER_EAGLE-LTSPICE_R0402
R2-USB: 5K1; ESP32_WROVER_EAGLE-LTSPICE_R0402
R2-USB1: 5k1; ESP32_WROVER_EAGLE-LTSPICE_R0402
R2_BAT: 2K; ESP32_WROVER_EAGLE-LTSPICE_R0402
R3: 0.47; ESP32_WROVER_EAGLE-LTSPICE_R0402
RESET_BUTTON: BUTTON_CUSYOMV1; MYBUTTON
RX_TP2: TPTP20R; TP20R
R_BOOT: 10K; ESP32_WROVER_EAGLE-LTSPICE_R0402
R_CAPACITOR: 15; ESP32_WROVER_EAGLE-LTSPICE_R0402
R_CHANGE: 10K; ESP32_WROVER_EAGLE-LTSPICE_R0402
R_CL1: 10k; ESP32_WROVER_EAGLE-LTSPICE_R0402
R_RESET: 10K; ESP32_WROVER_EAGLE-LTSPICE_R0402
SCK_TP8: TPTP20R; TP20R
SENSOR2: ESP32_WROVER_BME680_BME680; ESP32_WROVER_BME680_PSON80P300X300X100-8N
SJ1: SJ
TX_TP1: TPTP20R; TP20R
U1: ESP32_WROVER_SPARKFUN-IC-POWER_MCP73831; ESP32_WROVER_SPARKFUN-IC-POWER_SOT23-5
U2: ESP32-C6-WROOM-1-N8; XCVR_ESP32-C6-WROOM-1-N8
U3: DS3231SN#; SOIC127P1032X265-16N
U4: MAX17048G+T10; SON50P200X200X80-9N
U5: W25Q512JVEIQ; SON127P600X800X80-9N
VBAT_TP3: TPTP20R; TP20R
VBUS_TP14: TPTP20R; TP20R

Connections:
3V3: 3V3_TP16.TP, C1_BAT2.1, C3.+, C9.1, D7.2 (ANODE), IC1.2 (VDD), IC4.5 (VOUT), J3.2, J4.P4 (VDD), Q2.3 (D), R1.1, R1-PINH1.2, R2-PINH1.2, R_BOOT.1, R_CHANGE.1, R_CL1.1, R_RESET.1, U2.2 (3V3), U3.2 (VCC), U5.3 (!WP!(IO2)), U5.7 (!HOLD!/!RESET!(IO3)), U5.8 (VCC)
32KHZ: R2-PINH1.1, U2.9 (IO1), U3.1 (32KHZ)
DN: D1.4 (I/O2_2), J2.A7, J2.B7
DP: D1.6 (I/O1_2), J2.A6, J2.B6
EPD_3V3: C7.1, EPD_3V3_TP17.TP, EPD_C5.1, J1.15, J1.16, L1.2, Q2.2 (S)
EPD_3V3_C: EPD_3V3_C_TP13.TP, Q2.1 (G), R_CL1.2, U2.18 (IO20)
EPD_BUSY: EPD_BUSY_TP9.TP, J1.9, U2.26 (IO3)
EPD_CS: D6.2, EPD_CS_TP10.TP, J1.12, R9.1, U2.11 (IO10)
EPD_DC: EPD_DC_TP11.TP, J1.11, U2.5 (IO5)
EPD_RST: EPD_RST_TP12.TP, J1.10, U2.21 (IO23)
FLASH_CS: D9.2, R5.1, U2.12 (IO11), U5.1 (!CS)
GDR: J1.2, Q3.1 (G), R4.1
GPIO8: R1.2, U2.10 (IO8)
I2C_PW: C1.1, C2.1, R1-PINH.2, R2-PINH.2, SENSOR2.2 (CSB), SENSOR2.6 (VDDIO), SENSOR2.8 (VDD), U2.17 (IO19)
INT_RTC: INT_RTC_TP15.TP, R1-PINH1.1, U2.8 (IO0), U3.3 (SQW/!INT)
IO/BOOT: BOOT_BUTTON.3, BOOT_BUTTON.4, C6.1, R_BOOT.2, U2.15 (IO9)
IO/CHANGE: C10.1, CHANGE_BUTTON.3, CHANGE_BUTTON.4, R_CHANGE.2, U2.23 (IO15)
MISO: D12.2, J4.P7 (DAT0), MISO_TP6.TP, R8.1, U2.27 (IO2), U5.2 (DO(IO1))
MOSI: D11.2, J1.14, J4.P3 (CMD), MOSI_TP7.TP, R7.1, U2.7 (IO7), U5.5 (DI(IO0))
unnamed: C1_BAT1.1, D2.1 (CATHODE), IC4.1 (VIN), IC4.3 (CE), Q1.2 (S)
unnamed: J2.A5, R2-USB1.2
unnamed: R5.2, R6.2, R7.2, R8.2, R9.2, R10.2
unnamed: R1_BAT.1, U1.1 (STAT)
unnamed: C4.1, D3.2 (A), D4.1 (K)
unnamed: CHG_LED.C, R1_BAT.2
unnamed: D7.1 (CATHODE), R_CAPACITOR.1
unnamed: J2.B5, R2-USB.1
unnamed: C_DELAY.1, IC1.5 (CT)
unnamed: EPD_C12.1, J1.24
unnamed: R2_BAT.2, U1.5 (PROG)
unnamed: EPD_C8.1, J1.20
unnamed: EPD_C10.1, J1.22
unnamed: EPD_C7.1, J1.19
unnamed: EPD_C6.1, J1.18
unnamed: EPD_C1.1, J1.4
unnamed: EPD_C2.1, J1.5
PREVGH: D5.1 (K), EPD_C9.1, J1.21
PREVGL: D4.2 (A), EPD_C11.1, J1.23
RESE: J1.3, Q3.2 (S), R3.1
RESE': R2.2, R3.2, SJ1.2
RESET: C5.1, IC1.1 (VOUT), RESET_BUTTON.3, RESET_BUTTON.4, R_RESET.2, U2.3 (EN)
RTC_RST: U2.16 (IO18), U3.4 (!RST)
RX: RX_TP2.TP, U2.24 (RXD0/GPIO17)
SCK: D10.2, J1.13, J4.P5 (CLK), R6.1, SCK_TP8.TP, U2.6 (IO6), U5.6 (CLK)
SCL: J3.4, R2-PINH.1, SENSOR2.4 (SCK), U2.20 (IO22), U3.16 (SCL), U4.7 (SCL)
SDA: J3.3, R1-PINH.1, SENSOR2.3 (SDI), U2.19 (IO21), U3.15 (SDA), U4.8 (SDA)
SRC: C4.2, D5.2 (A), L1.1, Q3.3 (D)
SS_SD: D8.2, J4.P2 (CD/DAT3), R10.1, U2.4 (IO4)
TX: TX_TP1.TP, U2.25 (TXD0/GPIO16)
USB_D+: D1.1 (I/O1_1), U2.14 (IO13)
USB_D-: D1.3 (I/O2_1), U2.13 (IO12)
VBAT: C2_BAT.1, Q1.3 (D), U1.3 (VBAT), U4.2 (CELL), U4.3 (VDD), VBAT_TP3.TP
VBUS: C1_BAT.1, C4_USB.1, C5_USB.1, CHG_LED.A, D1.5 (VBUS), D2.2 (ANODE), PFMF.050.1.2, Q1.1 (G), R1_PWRUSB.2, U1.4 (VIN), VBUS_TP14.TP
VUSB: J2.A4, J2.A9, J2.B4, J2.B9, PFMF.050.1.1

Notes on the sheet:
USB C connector & ESD protection
LDO Voltage Regulator
SD Card
ESP32 C6
Display Type Selector
E-Paper Drive Circuit
Li-Po Battery Charging Controller
E-Paper Display Header
EPD Power
Environmental Sensor BME688
Voltage Supervisor + Reset & Boot / IO Button
Battery Charge Level
RTC Module S3231SN
Test Pads
Qwiic / Stemma QT
SPI ESD Protection Lines
External NOR Flash 64MB

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
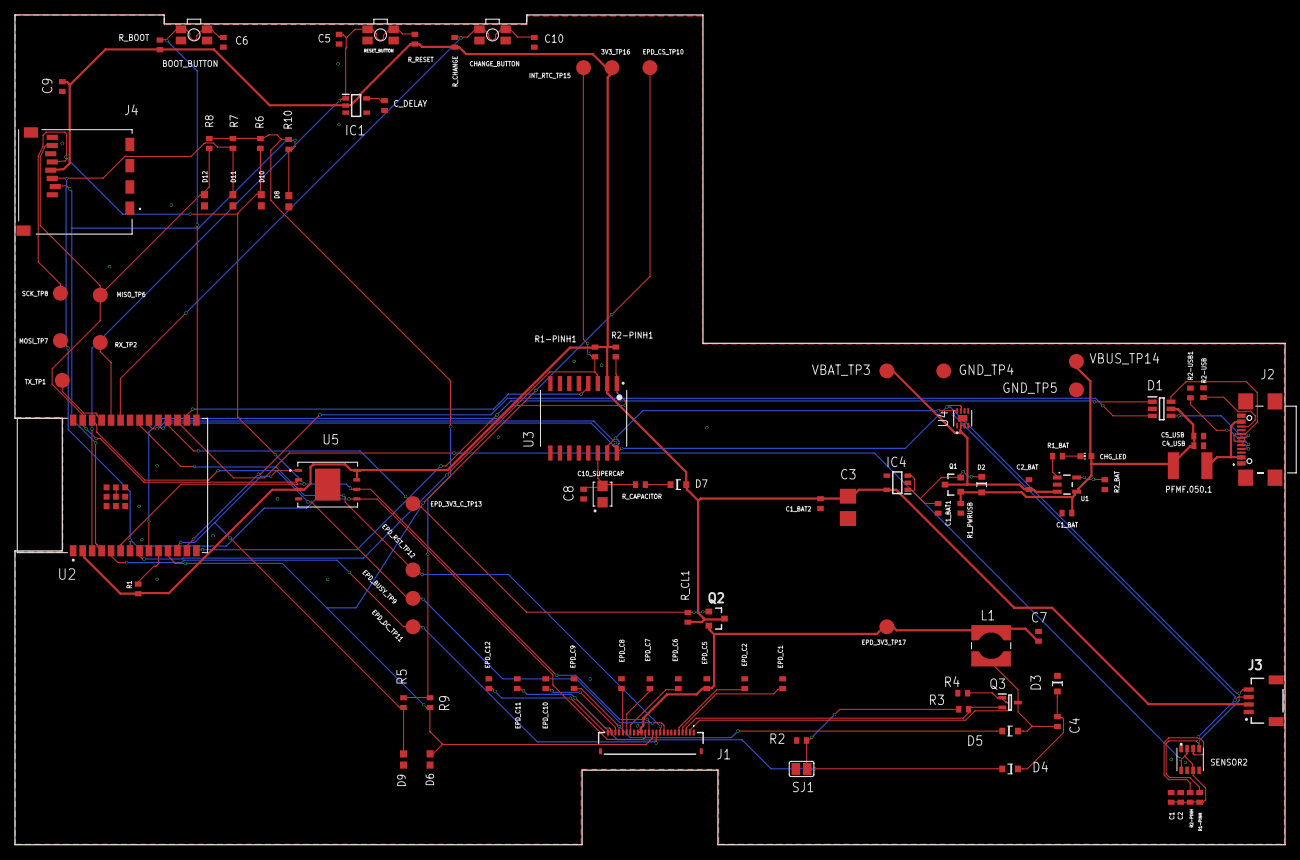
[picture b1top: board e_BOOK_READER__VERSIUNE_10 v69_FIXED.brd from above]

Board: 2 copper layers, 170.2 x 111.2 mm, 103 parts (0 on the bottom side), 56 nets.

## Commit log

2025-04-04 Create LICENSE
2025-04-10 Fixed update for 3D

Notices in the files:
parts and their libraries:
DeskAssistant v19 v1: COPYRIGHT: Copyright (C) 2024 Ultra Librarian. All rights reserved.
